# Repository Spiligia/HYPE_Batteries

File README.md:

**Boston University EC 463 & 464 Senior Design Project**

Members: Spencer Piligian, Ismaeel AlAlawi, Steven Wang, Yusheng Chen and Daniel Kao

## Welcome to Team 23: HYP Batteries! 

Our hybrid-chemistry battery pack design aims to fill niche market gap in high performance battery pack for small aircraft by combining two batteries with two different discharge characteristics. These two cell chemistries can achieve a variable-max discharge rate, allowing us to design a smaller battery pack while also fulfilling power requirements during the launch. This pack setup will help eGliders achieve a safe flight through the use of electric power and as a result, will minimize the risk of mechanical failure for our client’s conventional mechanical engines, whose vibration causes other parts of the aircraft to wear out and ultimately increases the chance of failure.

Link to google drive for more information / process development 

https://drive.google.com/drive/u/0/folders/0AN8LmBJzQ7HJUk9PVA

For member access please email: spiligia@bu.edu

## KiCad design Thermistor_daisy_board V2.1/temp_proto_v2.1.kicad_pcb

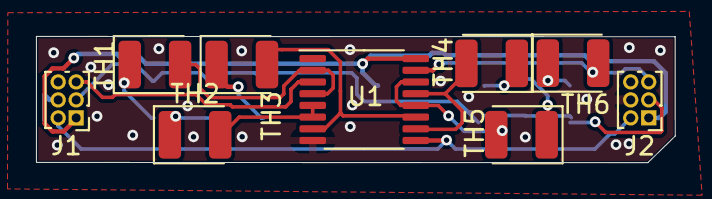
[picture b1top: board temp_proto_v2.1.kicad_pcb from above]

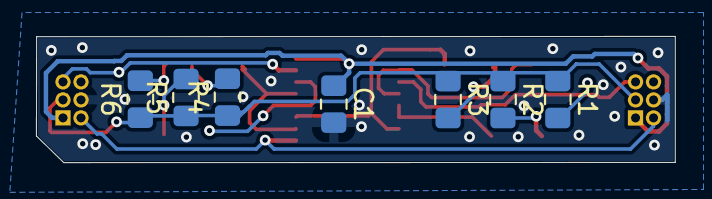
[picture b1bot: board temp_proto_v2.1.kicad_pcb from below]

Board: 2 copper layers, 35.5 x 7.0 mm, 16 parts (7 on the bottom side), 17 nets.

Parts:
C1: CAP; C_0805_2012Metric_Pad1.15x1.40mm_HandSolder
J1, J2: Conn_02x03_Counter_Clockwise; PinHeader_2x03_P1.00mm_Vertical
R1, R2, R3, R4, R5, R6: R_US; R_0805_2012Metric_Pad1.15x1.40mm_HandSolder
TH1, TH2, TH3, TH4, TH5, TH6: Thermistor_NTC; LED_1210_3225Metric
U1: Hex_d_ff_; TSSOP-16_4.4x5mm_P0.65mm

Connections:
CLK: J1.2, J2.2, U1.9
CONN_1: TH1.2, U1.2, U1.4
CONN_2: TH2.2, U1.5, U1.6
CONN_3: TH3.2, U1.7, U1.11
CONN_4: TH4.2, U1.10, U1.13
CONN_5: TH5.2, U1.12, U1.14
CONN_IN: J1.5, U1.3
CONN_OUT: J2.5, TH6.2, U1.15
GND: C1.2, J1.4, J2.4, U1.8
unnamed: R1.2, TH1.1
unnamed: R2.2, TH2.1
unnamed: R3.2, TH3.1
unnamed: R4.2, TH4.1
unnamed: R5.2, TH5.1
unnamed: R6.2, TH6.1
TEMP_REF: J1.3, J2.3, R1.1, R2.1, R3.1, R4.1, R5.1, R6.1
VCC: C1.1, J1.1, J2.1, U1.16

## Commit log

2022-01-26 Code for temp control
    Using an arduino BLE
2022-01-26 udpate name
2022-01-26 .ino ext added
2022-01-27 updated some values for base arduino
    1023bit for non ble arduinos - may use megas
2022-02-01 output update
    set output text to serial monitor if over temp
2022-04-15 Renders of Thermistor cell boards
    - add grbr/ kicad files
2022-04-15 Create BatteryDisplay
    App for Battery Display
2022-04-15 Add files via upload
    Battery Display App
2022-04-16 Design files for thermistor daisy chain boards
    Done in KiCad verion 6. Full data for print GBR/Drill
2022-04-17 Create README_SOFTWARE.md
    added software readme
2022-04-17 Rename README.md to README_HARDWARE.md
    changed to hardware to distinguish both README files
2022-04-17 Create battery_testbench_v1.00.lisp
    Automated battery pack testbench using Lisp
2022-04-18 Ideal Diode Controller PCB
2022-04-18 Thermistor daisy board unzipped
    + read_me
2022-04-26 add files
2022-04-27 Updated heatmapimageprovider.cpp
    add additional json array variable and how the data will draw uonto the map
2022-04-29 Add files via upload
    naive testbench for motor current control
2022-04-29 Delete Directory
    File names contain spaces, causing failiure to pull needs to be re named
2022-04-29 update software readme
2022-04-29 pcis
2022-04-29 pics
    pics
2022-04-29 pics
2022-04-29 Delete 3D_Battery_holders directory
    pull issue
2022-04-30 Delete Prototype_Test directory
    Directory has space " prototype_test(space)" error pulling
